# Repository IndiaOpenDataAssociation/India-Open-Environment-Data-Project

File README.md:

# India-Open-Environment-Data-Project
All the necessary details about the project such as the design and assembly of environment monitoring devices, the server settings and the front-end programming for visualization are all avaliable here.
The data is bound by Creative Commons licence (Attribution-NonCommercial-ShareAlike). Anyone who wishes to replicate the project or utilize it for further development can do so.

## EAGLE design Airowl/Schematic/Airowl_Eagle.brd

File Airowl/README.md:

AirOwl
======
Airowl is a D-i-Y (Do-it-Yourself) kit which helps you to build your own personal Air Quality Monitoring device. The device would give you real-time air quality data on the app and update you of the air that you are breathing.

Wikipedia link For all the information about : [AirOwl](http://knowledge.indiaopendata.com/index.php/AirOwl)

Details about folder content : 

 **Design** :  It contains all the design file of AirOwl.

**Firmware :** It contains firmware for AirOw 3G and AirOwl Wi. It also has FAQ related to AirOwl.

**Schematic :** It contains schematic files for AirOwl PCB, You can download and print it your self.

Features :
----------

**Easy to assemble:**
Trust us, it is as easy as making something out of the lego toys.

**Low cost:**
You need not to spend your entire savings into it. We value your money!

**Portable(handy):**
Don’t worry, you can carry it anywhere and everywhere.

**One touch data access:**
Even we don’t like to waste time.

**User-friendly/centric mobile app:**
We like to keep it simple.
    
**Accurate:**
The devices are calibrated for hours and we have tried our best to get highest accuracy.

**D-i-Y kit:**
Trust us, it is as easy as making something out of the lego toys.

How to assemble your owl :

How to setup your owl :

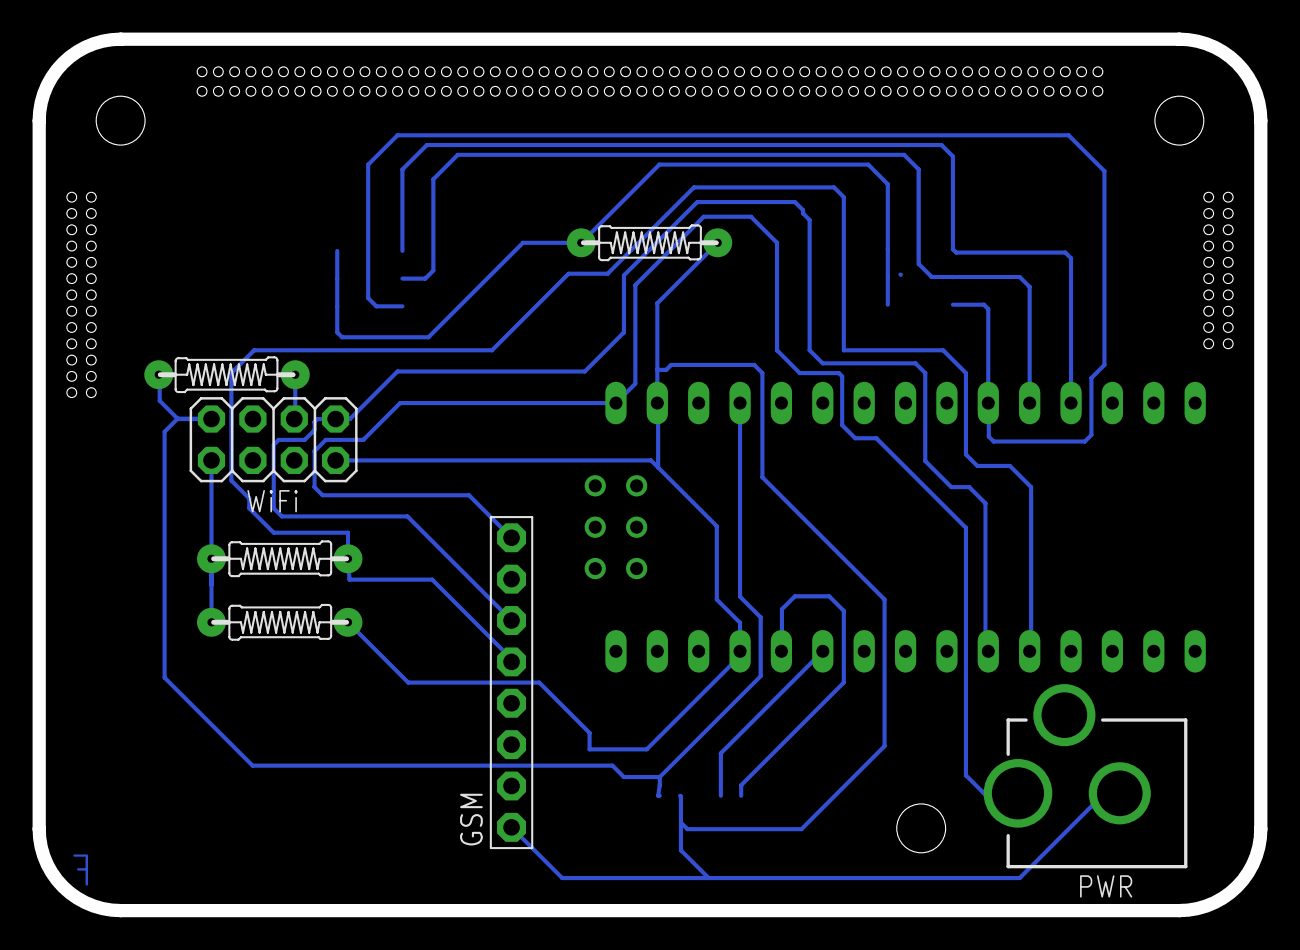
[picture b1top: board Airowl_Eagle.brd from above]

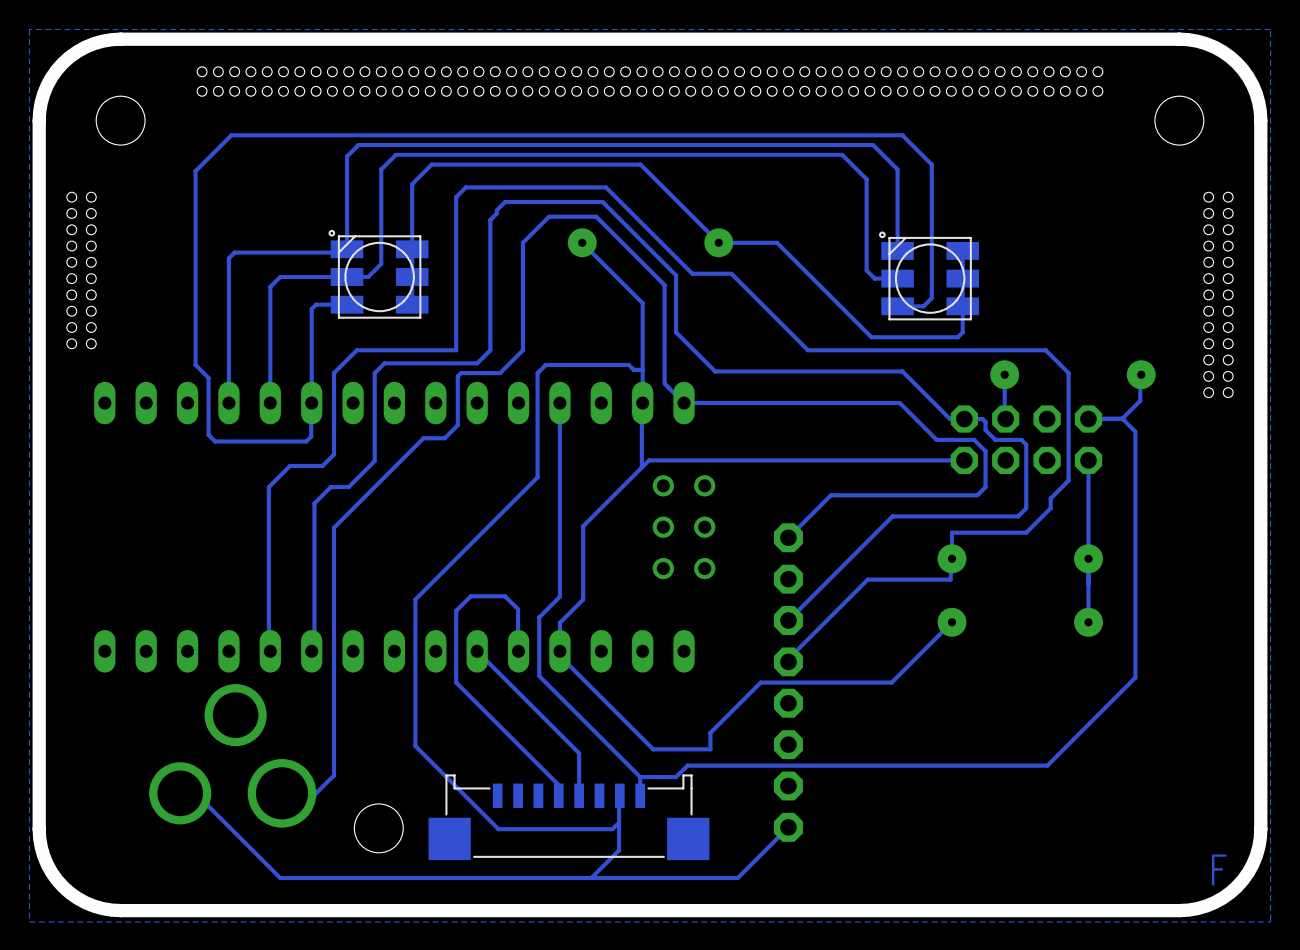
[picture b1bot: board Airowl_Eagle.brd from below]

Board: 2 copper layers, 75.0 x 53.5 mm, 11 parts (3 on the bottom side), 13 nets.

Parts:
E$1: NANO
E$2: WINSEN_CONNECTOR
E$3, E$5: RGBLED5050
E$4: 2X04
E$6, E$7, E$8, E$9: RESISTER(HORIZONTAL)
GSM: 1X08-BIG
PWR: DCJACK_2MM_PTH

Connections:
5V: E$1.5V, E$2.P$9, E$4.7, E$7.1
GND: E$1.GND, E$1.GND1, E$2.P$8, E$4.2, E$6.1, E$9.1, GSM.1, PWR.GND
PWR: E$1.RAW, GSM.8, PWR.PWR
S$1: E$3.1, E$3.2, E$3.3, E$5.1, E$5.2, E$5.3, E$6.2
S$3: E$1.A1, E$3.5, E$5.5
S$6: E$1.A0, E$3.4, E$5.4
S$7: E$1.A2, E$3.6, E$5.6
S$8: E$1.D7, E$4.1, GSM.6
S$9: E$1.D8, E$8.1, GSM.5
S$10: E$1.D3, E$2.P$6
S$11: E$1.D2, E$2.P$5
S$12: E$4.3, E$7.2
S$13: E$4.8, E$8.2, E$9.2

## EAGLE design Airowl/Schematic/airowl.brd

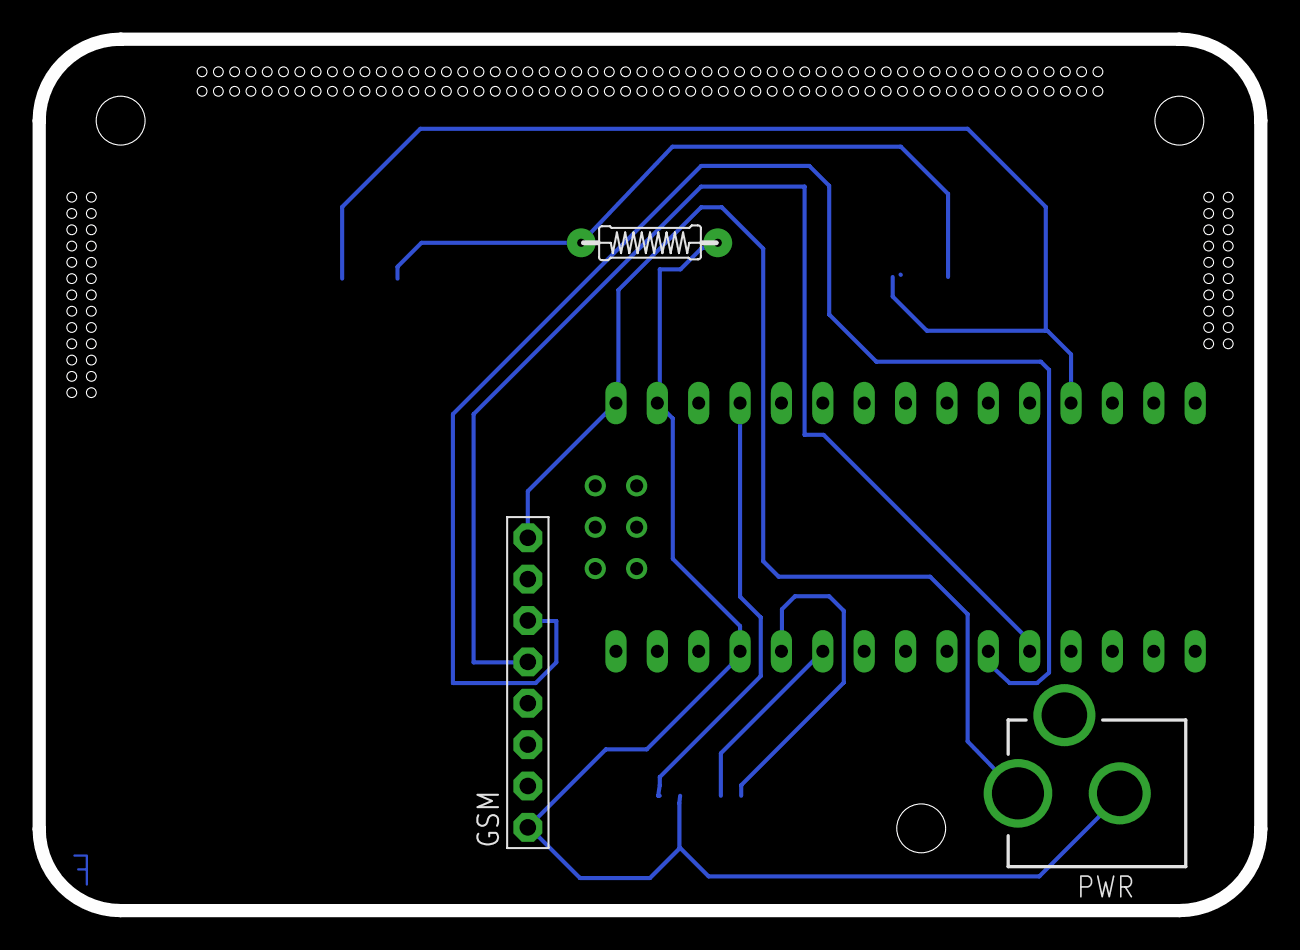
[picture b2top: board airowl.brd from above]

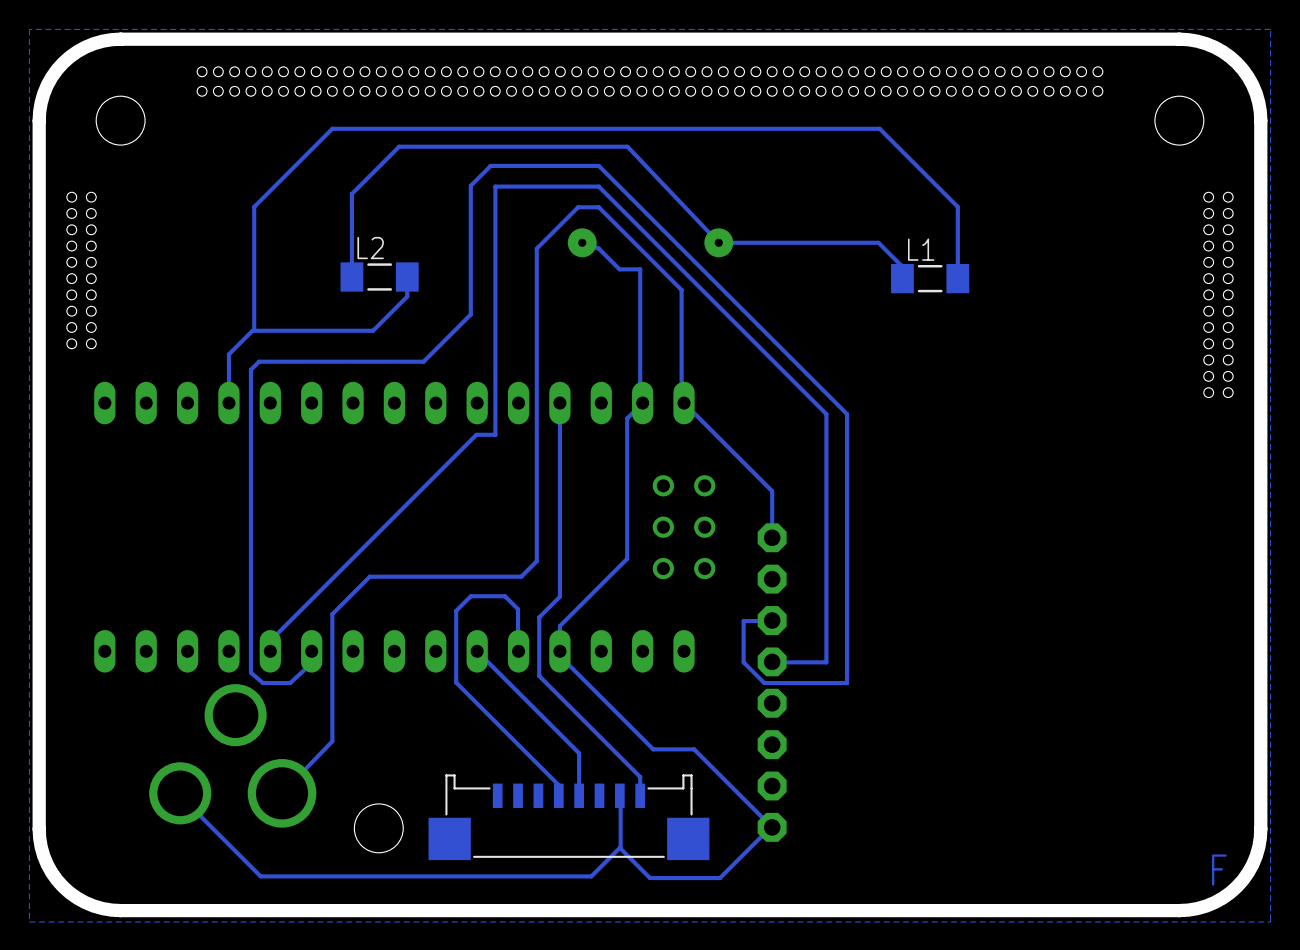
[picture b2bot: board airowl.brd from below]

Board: 2 copper layers, 75.0 x 53.5 mm, 7 parts (3 on the bottom side), 9 nets.

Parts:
E$1: NANO
E$2: WINSEN_CONNECTOR
E$6: RESISTER(HORIZONTAL)
GSM: 1X08-BIG
L1, L2: M3516
PWR: DCJACK_2MM_PTH

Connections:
GND: E$1.GND, E$1.GND1, E$2.P$8, E$6.1, GSM.1, PWR.GND
PWR: E$1.RAW, GSM.8, PWR.PWR
S$1: E$1.A0, L1.2, L2.2
S$2: E$6.2, L1.1, L2.1
S$4: E$1.5V, E$2.P$9
S$8: E$1.D7, GSM.6
S$9: E$1.D8, GSM.5
S$10: E$1.D3, E$2.P$6
S$11: E$1.D2, E$2.P$5

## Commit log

2016-03-29 removed
2016-05-20 Removing Folders
2016-05-20 Removing Readme file
2016-05-20 Adding AirOwl Files
    Adding 3 folders:-
    - Firmware containing the Code for Collection of data and Uploading it to the server.
    - Schematic for the PCB and printed silkscreen.
    - Design for the Acrylic structure.
2016-05-20 Adding AirOwl Files
    Adding 3 folders:-
    - Firmware containing the Code for Collection of data and Uploading it to the server.
    - Schematic for the PCB and printed silkscreen.
    - Design for the Acrylic structure.
2016-05-20 Adding new pollution platform in angularjs
2016-05-20 Adding node_modules, bower_components and dist
2016-05-20 adding gitignore file
2016-05-20 updating opendatamap readme.md
2016-05-21 OpenDataMap : changing field constants
2016-05-21 fixed untracked files
2016-05-21 Removing unwanted files
2016-05-21 OpenDataMap : airowl page banner background issue solved'
2016-05-21 Opendatamap : airowl page adding
2016-05-21 OpenDataMap: adding airowl in header
2016-05-21 Changing casing image in airowl
2016-05-23 OpenDataMap : Airowl text changes
2016-05-23 Changin swagger url
2016-05-23 Step one in Making dashboard responsive
2016-05-24 Making site responsive. Menu icon still to be worked out
2016-05-24 finished making website responsive. Menu button problem solved.
2016-05-30 stopping redirection of airpollution.online
2016-05-30 changing open environment project title
2016-06-01 Changing project title
2016-06-01 getting ready for economic times iframe
2016-06-01 economic times version 1 ready
2016-06-01 pins changed
2016-06-01 changing bottom panel css
2016-06-01 type showing at airpollution online select device
2016-06-01 side pan title change
2016-06-01 All fields check for cpcb type, compulsory changes done in frontend
2016-06-01 max aqi instead of average, analytics subtitle, fields check
2016-06-01 Adding analytics changes
2016-06-01 adding all the changes in airowl page
2016-06-01 responsive changes'
2016-06-02 Adding responsive changes
2016-06-02 gases value priority changed
2016-06-02 adding bug fix controller
2016-06-02 gas parameters bugs resolved:
2016-06-03 Changes on airowl page
2016-06-03 deleting unnecessary
2016-06-03 social share work going on, other css chagnes done'
2016-06-03 Adding India in center as per ankur's request
2016-06-03 Adding as of instead of updated at text
2016-06-03 adding loader page
2016-06-03 pins changed again and facebook sharing working
2016-06-03 final version of pins
2016-06-03 adding twitter share
2016-06-03 Adding new pins for locatioin
2016-06-03 adding development version facebook sharing id
2016-06-03 adding some airowl changes
2016-06-03 instamojo integration on airowl page
2016-06-03 old changes of airpollution title rechange
2016-06-04 adding airowl wiki knowledge page
2016-06-04 Airowl_3G & Airowl_wifi
    Airowl 3G and wifi code updated
2016-06-04 Adding htaccess for refresh issue solve, other dashboard changes, compression of js and css done
2016-06-04 images compressed, github and wiki link in airowl page, city changed to india
2016-06-04 Adding all the changes for airowl page
2016-06-04 adding htaccess for html5mode
2016-06-04 google analytics added
2016-06-06 airowl price tag, partners image change
2016-06-07 changing airowl page cover pic.
2016-06-08 adding modernizer.js, classie.js reference in index cover page changes in airowl.html zoom control repostioned in google-map and some minor css changes
2016-06-09 setting up leaflet map without any markers.
2016-06-09 markers added to map without custom icons
2016-06-09 city wise navigation in the map working
2016-06-09 adding script for google analytics
2016-06-10 leaflet maps everything working fine. css of bottom nav icons to be fixed.
2016-06-10 fixed three bottom nav buttons.
2016-06-10 LED blinking set
2016-06-10 AirOwl Wifi : LED Support added
2016-06-13 migration from google maps to leaflet
2016-06-14 Led Blinking.
    Led Blinking.
2016-06-14 Minor corrections
2016-06-15 marker clustering
2016-06-15 correction
2016-06-17 LED blinks on code upload
2016-06-17 Delay in data sending
2016-06-18 working code
2016-06-18 Revert "correction"
    This reverts commit fe9c8fe2f7ef7e656b8aa76eed658e0088d58288.
2016-06-18 Final working
2016-06-20 Device Id is set
2016-06-20 code regulation changes
2016-06-21 Change in format. Working code.
2016-06-23 Added stable firmware for AirOwl Wi
2016-06-23 Updated Stable AirOwl Wi Firmware
2016-06-23 AirOwl 3G Firmware stable update
2016-06-23 Create Airowl
2016-06-27 Update Airowl_3G.ino
    Updated AirOwl 3G firmware
2016-06-27 Updated Stable AirOwl 3G Firmware
2016-06-28 updated data sending timer
2016-06-30 Final working codes
2016-06-30 Final working code
2016-07-04 AirOwl Server name update
2016-07-04 Server name updated
2016-07-04 Final working code.
2016-07-04 Create README File
2016-07-04 Updated README file
2016-07-04 For resetting Baudrate
2016-07-04 Updated Manuals
2016-07-04 Updated Manuals and Folder details
2016-07-04 Updated file positions
2016-07-07 airowl page restructured
2016-07-08 changing airowl page final
2016-07-21 Responsive code
2016-07-21 adding some bug free code
2016-07-29 dashboard.controller.js filename changed and changing UI elements
2016-07-30 adding responsive css and html
2016-08-01 Few updates on AP mode
2016-08-01 Changes in names
2016-08-01 overlay added and airowl links updated
2016-08-10 Update dust checksum code
2016-08-12 Updated Dust sensor function
2016-08-12 Update function name
2016-08-12 Syntax change
2016-08-12 Syntax update
2016-08-19 init code
2016-08-19 Rename file
2016-08-19 removing unwanted scripts from here
2016-09-04 Updated Limits for lights
2016-09-28 started using new apis
2016-09-28 mashape apis added
2016-09-28 new apis added according to backend
2016-10-07 Created new version of AirOwl firmware
2016-10-17 Added AT Command Link
2016-11-15 Codebase changed to react
2016-11-15 to avoid babel issues in ubuntu, added babelrc
2016-11-15 adding readme description
2016-11-15 boilerplate files removing
2017-02-20 Create AirOwl_v3.ino
    NodeMcu based AirOwl code, which do not require any mobile app to configure your AirOwl.
2017-06-22 Remove the AirOwl project
2017-06-22 Remove OpenDataMap project
